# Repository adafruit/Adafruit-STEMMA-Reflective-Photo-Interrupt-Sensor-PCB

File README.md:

## Adafruit STEMMA Reflective Photo Interrupt Sensor - TCRT1000 PCB

<a href="http://www.adafruit.com/products/5913"><br/>
Click here to purchase one from the Adafruit shop</a>

PCB files for the Adafruit STEMMA Reflective Photo Interrupt Sensor - TCRT1000. 

Format is EagleCAD schematic and board layout
* https://www.adafruit.com/product/5913

### Description

An optical reflective sensor is a composite electronic device with two elements - an IR LED and an IR photo-transistor. The IR LED blasts light, and when something bounces the light back to the photo-transistor, the transistor turns on and the amount of current flowing through it increases. This makes the sensor great at detecting when something is in front of the sensor: when nothing is there the IR light never gets reflected back and the transistor stays off.

We have two versions of this sensor that are 'breadboard' friendly, the ITR20001 and a chunky all-in-one Infrared Reflective Sensor, but both are tough to mount, and require wiring up with resistors to get working. To make usage super fast and no-soldering-or-breadboarding-required, the Adafruit STEMMA Reflective Photo Interrupt Sensor is ready to go out of the box.

Power it with 3 to 5V DC and read the signal off the output pin to quickly detect reflective surfaces. A green LED tells you that the board is powered,  and a red LED will light up to let you know when the phototransistor is activated. (Both LEDs can be disabled)

Onboard we have a TCRT1000 right-angle sensor module. A potentiometer allows adjustment of how bright the IR emitter is, turn it all the way down for about 1mA, turn it all the way up for about 100mA. Then the receiving phototransistor is biased with a 10K pullup. When no IR light is detected, the output signal pin is high. When IR is bounced back, the voltage will drop down towards 0V.

This board has a simple plug-and-play JST PH (2mm pitch) input connector for solderless use. For use with a CircuitPlayground or micro:bit, this JST to alligator-clip cable works best. Red is power, ground is black and signal is white. For use with a breadboard, try this JST to male/plug-header. (We also have a socket-header cable if you want)

### License

Adafruit invests time and resources providing this open source design, please support Adafruit and open-source hardware by purchasing products from [Adafruit](https://www.adafruit.com)!

Designed by Limor Fried/Ladyada for Adafruit Industries.

Creative Commons Attribution/Share-Alike, all text above must be included in any redistribution. 
See license.txt for additional details.

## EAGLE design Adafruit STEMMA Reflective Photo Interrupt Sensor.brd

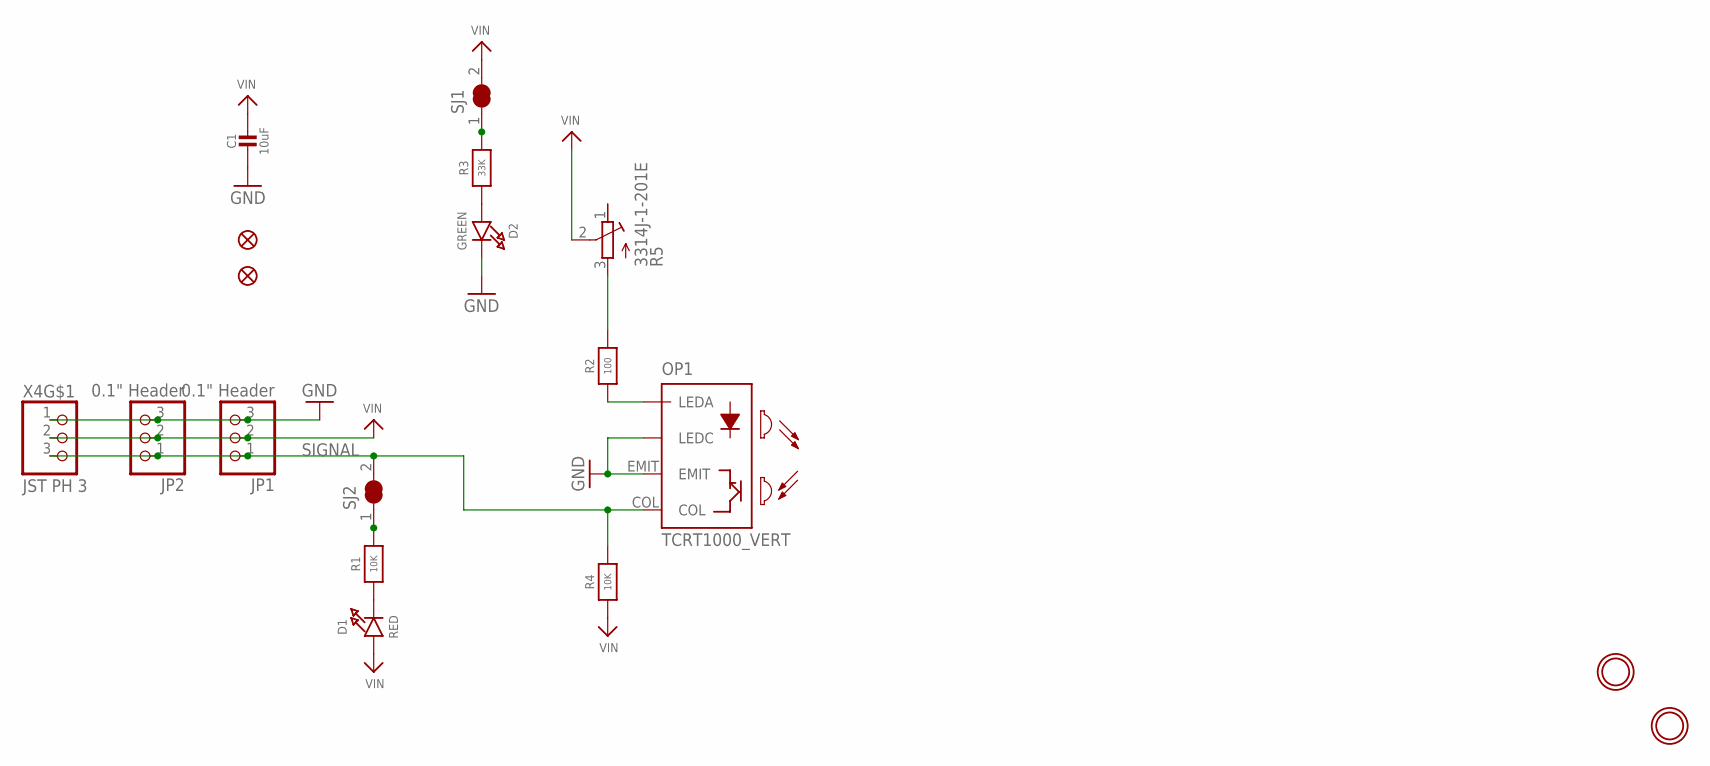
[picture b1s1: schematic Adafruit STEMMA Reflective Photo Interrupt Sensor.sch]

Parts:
C1: 10uF; 0805-NO
D1: RED; CHIPLED_0603_NOOUTLINE
D2: GREEN; CHIPLED_0603_NOOUTLINE
FID2, FID3: FIDUCIAL_1MM
JP1: 0.1" Header; 1X03_OVAL
JP2: 0.1" Header; 1X03_ROUND
OP1: TCRT1000_VERT; TCRT1000
R1, R4: 10K; 0603-NO
R2: 100; 0603-NO
R3: 33K; 0603-NO
R5: 3314J-1-201E; RTRIM3314J
SJ1, SJ2: SOLDERJUMPER_CLOSED; SOLDERJUMPER_CLOSEDWIRE
U$1, U$8: MOUNTINGHOLE2.5; MOUNTINGHOLE_2.5_PLATED
X4: JST PH 3; JSTPH3

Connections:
GND: C1.2, D2.C, JP1.3, JP2.3, OP1.EMIT, OP1.LEDC, X4.1
unnamed: R3.2, SJ1.1
unnamed: D1.C, R1.1
unnamed: R1.2, SJ2.1
unnamed: R2.2, R5.3 (A)
unnamed: OP1.LEDA, R2.1
unnamed: D2.A, R3.1
SIGNAL: JP1.1, JP2.1, OP1.COL, R4.2, SJ2.2, X4.3
VIN: C1.1, D1.A, JP1.2, JP2.2, R4.1, R5.2 (S), SJ1.2, X4.2

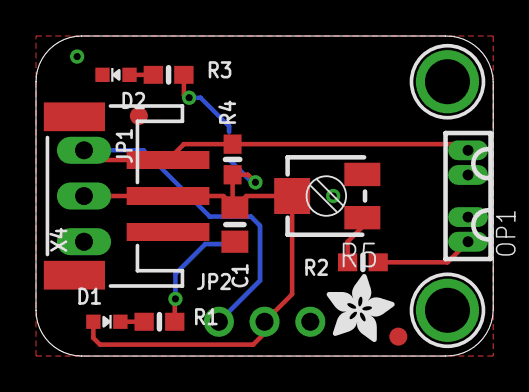
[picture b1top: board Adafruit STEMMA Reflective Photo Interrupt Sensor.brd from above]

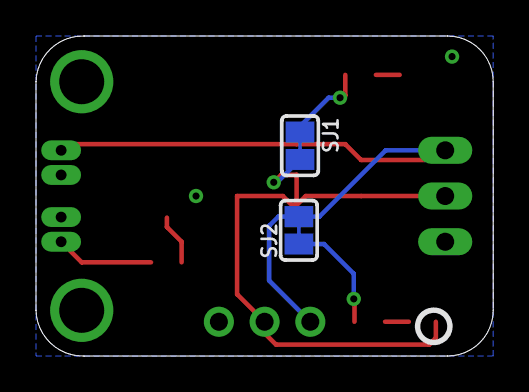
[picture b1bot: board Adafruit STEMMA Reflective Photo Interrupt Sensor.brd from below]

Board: 2 copper layers, 25.4 x 17.8 mm, 36 parts (12 on the bottom side), 9 nets.

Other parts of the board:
PLABEL0: PLABEL0
PLABEL1: PLABEL1
PLABEL7: PLABEL7
PLABEL8: PLABEL8
PLABEL9: PLABEL9
PLABEL10: PLABEL10
PLABEL11: PLABEL11
PLABEL12: PLABEL12
PLABEL13: PLABEL13
PLABEL14: PLABEL14
PLABEL15: PLABEL15
PLABEL16: PLABEL16
PLABEL17: PLABEL17
PLABEL18: PLABEL18
PLABEL19: PLABEL19
PLABEL20: PLABEL20
U$5: PCBFEAT-REV-040
U$10: ADAFRUIT_3.5MM

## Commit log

2024-04-02 cookiecutter

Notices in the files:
parts and their libraries:
microbuilder: This work is placed in the public domain, and may be freely used for commercial and non-commercial work with the following conditions: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
